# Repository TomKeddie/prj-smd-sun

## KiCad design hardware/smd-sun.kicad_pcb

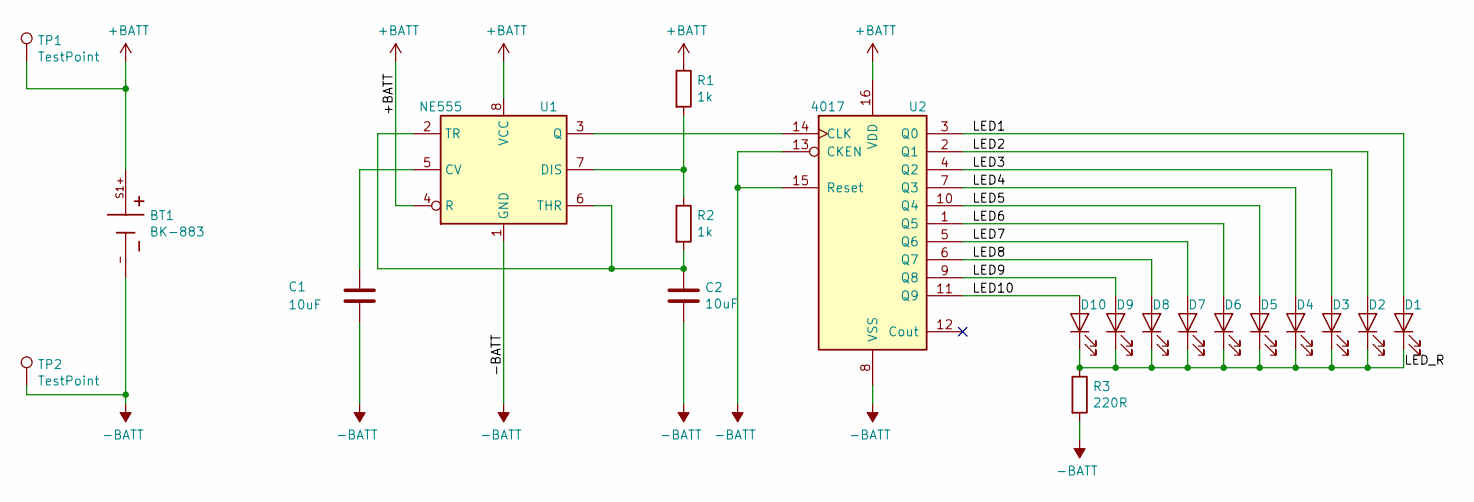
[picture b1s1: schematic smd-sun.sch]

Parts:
BT1: BK-883; BAT_BK-883
C1, C2: 10uF; C_0805_2012Metric_Pad1.15x1.40mm_HandSolder
D1, D2, D3, D4, D5, D6, D7, D8, D9, D10: LED; LED_0805_2012Metric_Pad1.15x1.40mm_HandSolder
R1, R2: 1k; R_0805_2012Metric_Pad1.15x1.40mm_HandSolder
R3: 220R; R_0805_2012Metric_Pad1.15x1.40mm_HandSolder
TP1, TP2: TestPoint; TestPoint_Pad_D3.0mm
U1: NE555; SO-8_3.9x4.9mm_P1.27mm
U2: 4017; SOIC-16_3.9x9.9mm_P1.27mm

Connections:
+BATT: BT1.S1+, BT1.S2+, R1.1, TP1.1, U1.4 (R), U1.8 (VCC), U2.16 (VDD)
-BATT: BT1.-, C1.2, C2.2, R3.2, TP2.1, U1.1 (GND), U2.8 (VSS), U2.13 (CKEN), U2.15 (Reset)
/LED1: D1.2 (A), U2.3 (Q0)
/LED2: D2.2 (A), U2.2 (Q1)
/LED3: D3.2 (A), U2.4 (Q2)
/LED4: D4.2 (A), U2.7 (Q3)
/LED5: D5.2 (A), U2.10 (Q4)
/LED6: D6.2 (A), U2.1 (Q5)
/LED7: D7.2 (A), U2.5 (Q6)
/LED8: D8.2 (A), U2.6 (Q7)
/LED9: D9.2 (A), U2.9 (Q8)
/LED10: D10.2 (A), U2.11 (Q9)
/LED_R: D1.1 (K), D2.1 (K), D3.1 (K), D4.1 (K), D5.1 (K), D6.1 (K), D7.1 (K), D8.1 (K), D9.1 (K), D10.1 (K), R3.1
unnamed: C1.1, U1.5 (CV)
unnamed: C2.1, R2.2, U1.2 (TR), U1.6 (THR)
unnamed: R1.2, R2.1, U1.7 (DIS)
unnamed: U1.3 (Q), U2.14 (CLK)

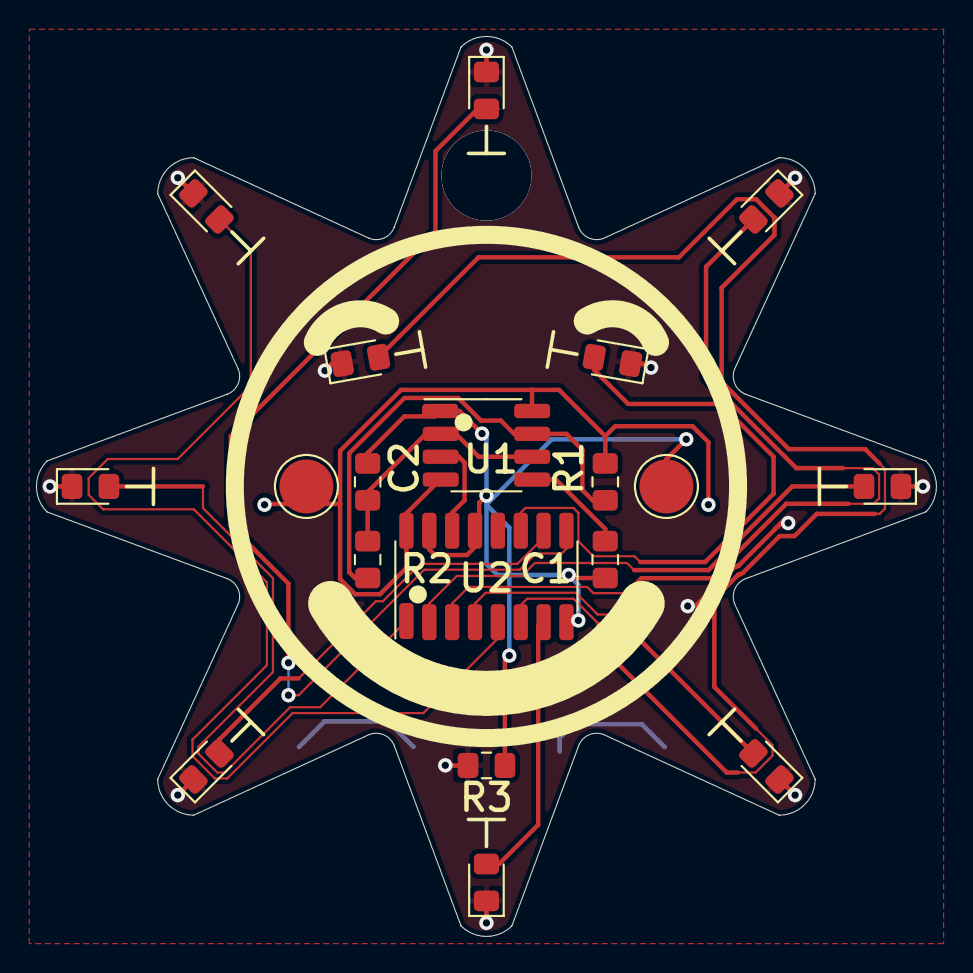
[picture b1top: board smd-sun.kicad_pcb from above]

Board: 2 copper layers, 50.0 x 50.0 mm, 20 parts (1 on the bottom side), 17 nets.

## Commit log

2020-07-02 Schematic almost complete (missing battery holder) PCB outline done (inner arc r=1mm, outer arc r=2mm)
2020-07-03 PCB Routed
2020-07-03 PCB - silk fixes, added missing hanging hole
2020-07-03 Rename all to smd-sun
2020-07-04 Hardware - fix 3d models
2020-07-20 Updates to July2020 pcb - fix silk clash on bottom layer - add front copper pour - enlarge cr2032 centre pad - move vias awaty from cr2032 centre pad
2020-12-13 Fix resistor values Enlarge SOIC pads to make soldering easier
2020-12-13 Add test points
2020-12-13 Add missing footprint file
2020-12-14 Add two test point for bringup, fix errata from Jun2020
